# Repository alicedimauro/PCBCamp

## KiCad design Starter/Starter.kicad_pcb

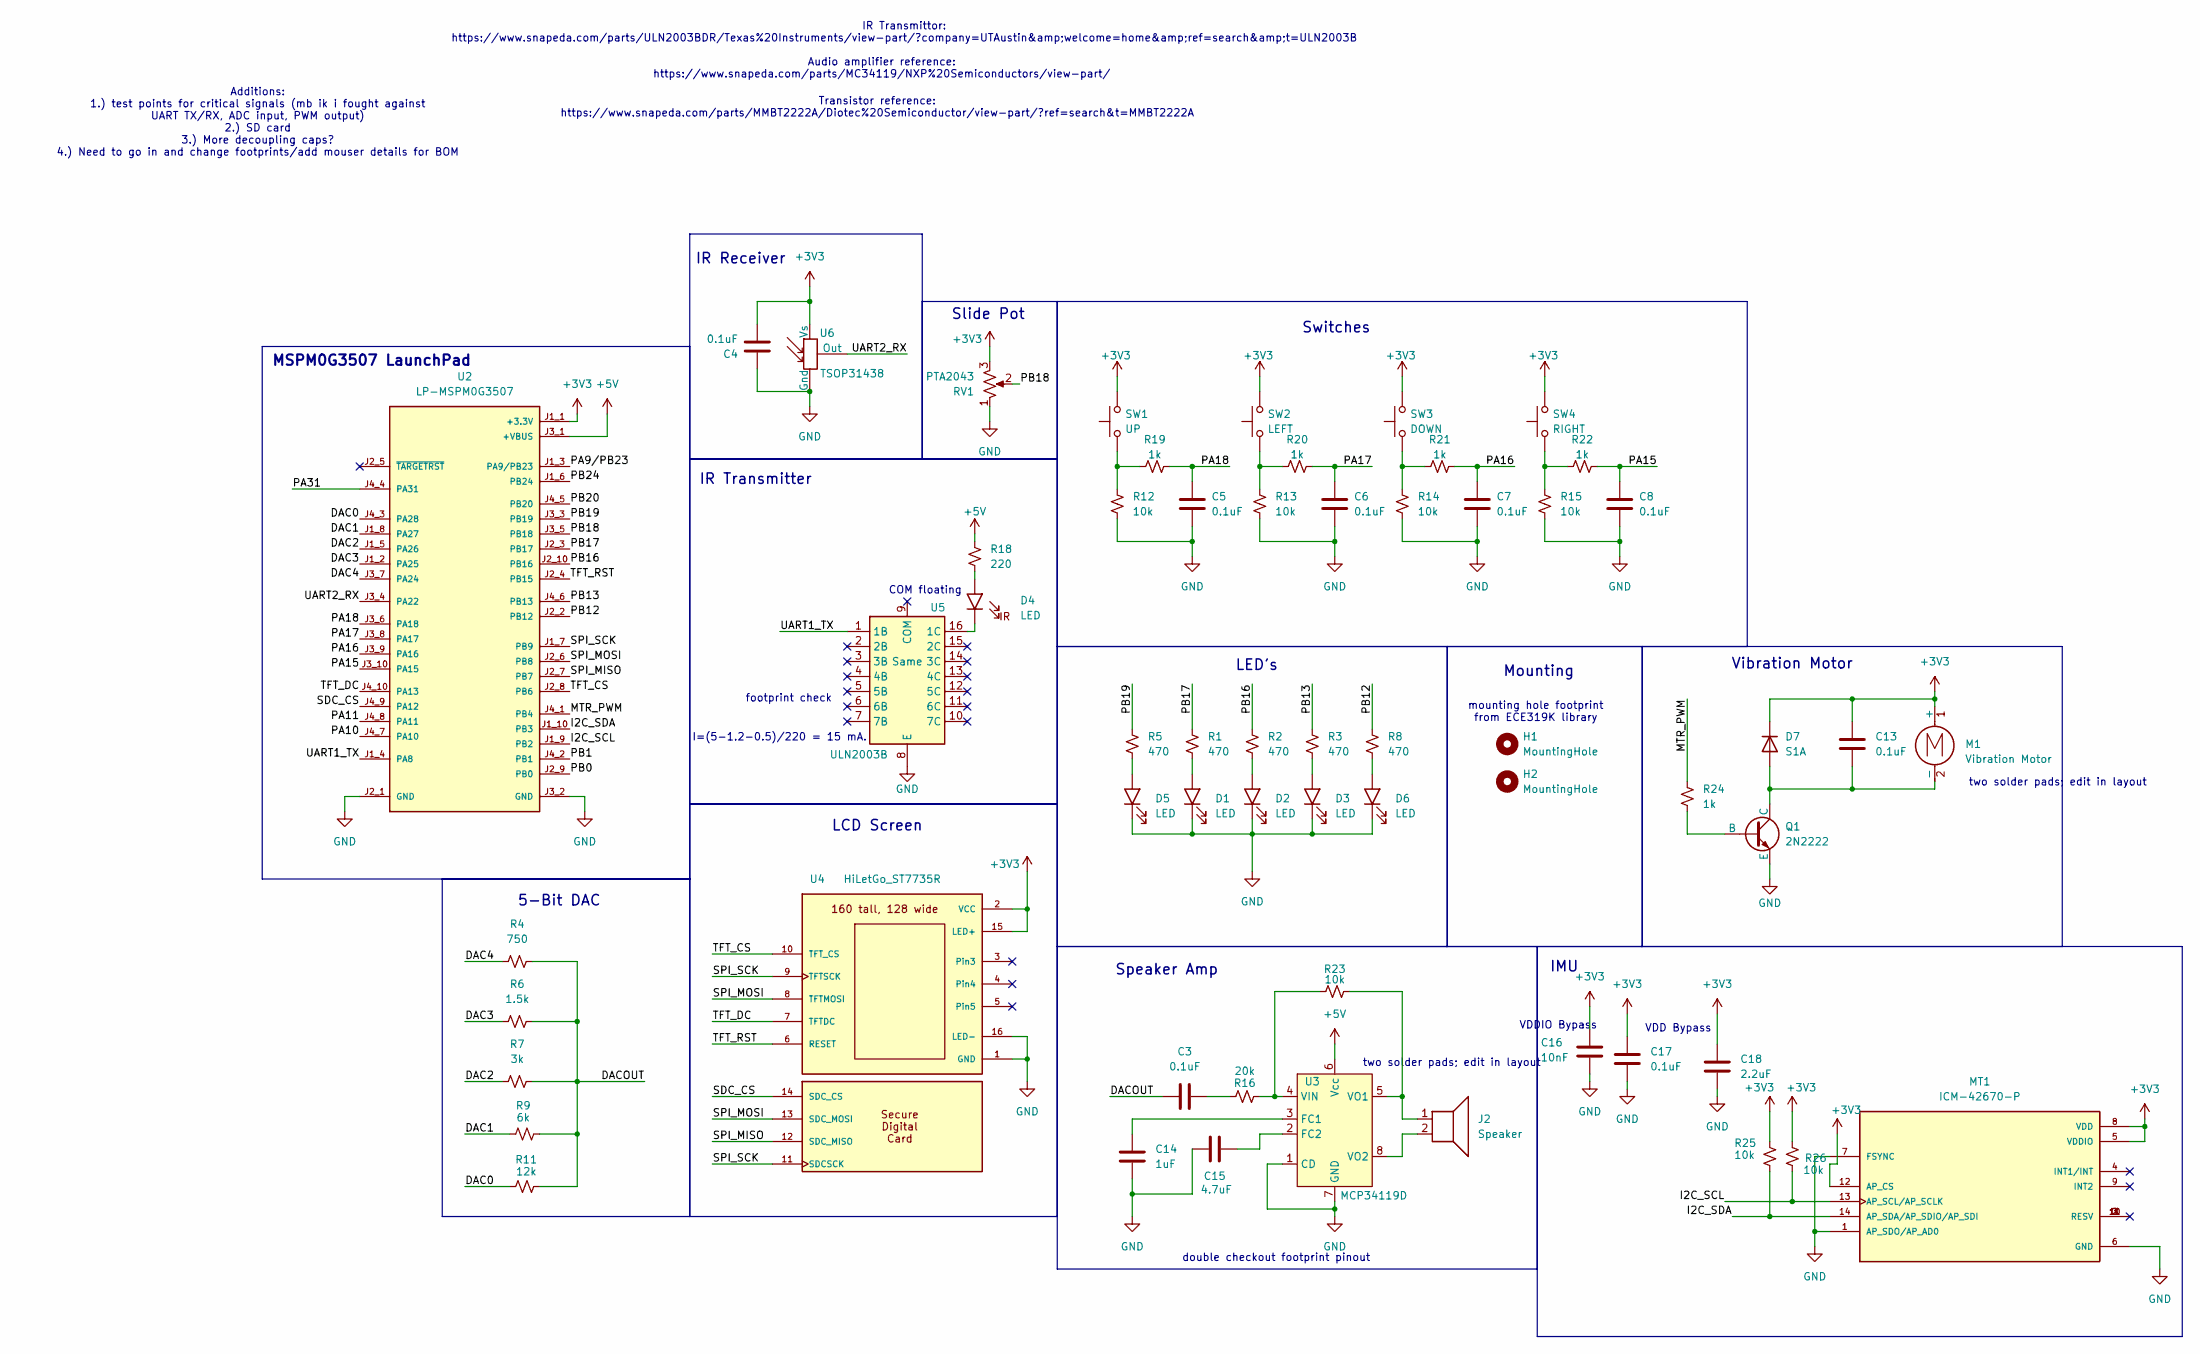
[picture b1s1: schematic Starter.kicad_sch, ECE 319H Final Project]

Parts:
C3, C4, C5, C6, C7, C8, C13, C17: 0.1uF; C_0603_1608Metric_Pad1.08x0.95mm_HandSolder
C14: 1uF; C_0603_1608Metric_Pad1.08x0.95mm_HandSolder
C15: 4.7uF; C_0603_1608Metric_Pad1.08x0.95mm_HandSolder
C16: 10nF; C_0603_1608Metric_Pad1.08x0.95mm_HandSolder
C18: 2.2uF; C_0603_1608Metric_Pad1.08x0.95mm_HandSolder
D1, D2, D3, D5, D6: LED; LED_0805_2012Metric
D4: LED; LED_D5.0mm
D7: S1A; D_SMA; Mouser # 512-S1A
H1, H2: MountingHole; MountingHole_3.2mm_M3
J2: Speaker; Testpoint_1x02_P2.54mm
M1: Vibration Motor; Testpoint_1x02_P2.54mm; Mouser # 316040001
MT1: ICM-42670-P; XDCR_ICM-42670-P; Mouser # 410-ICM-42670-P
Q1: 2N2222; SOT-23; Mouser # MMBT2222A
R1, R2, R3, R5, R8: 470; R_0603_1608Metric_Pad0.98x0.95mm_HandSolder
R4: 750; R_0603_1608Metric_Pad0.98x0.95mm_HandSolder
R6: 1.5k; R_0603_1608Metric_Pad0.98x0.95mm_HandSolder
R7: 3k; R_0603_1608Metric_Pad0.98x0.95mm_HandSolder
R9: 6k; R_0603_1608Metric_Pad0.98x0.95mm_HandSolder
R11: 12k; R_0603_1608Metric_Pad0.98x0.95mm_HandSolder
R12, R13, R14, R15, R23, R25, R26: 10k; R_0603_1608Metric_Pad0.98x0.95mm_HandSolder
R16: 20k; R_0603_1608Metric_Pad0.98x0.95mm_HandSolder
R18: 220; R_0603_1608Metric_Pad0.98x0.95mm_HandSolder
R19, R20, R21, R22, R24: 1k; R_0603_1608Metric_Pad0.98x0.95mm_HandSolder
RV1: PTA2043; PTA2043pot
SW1: UP; SW_SPST_PTS645; Mouser # 506-1977223-1
SW2: LEFT; SW_SPST_PTS645; Mouser # 506-1977223-1
SW3: DOWN; SW_SPST_PTS645; Mouser # 506-1977223-1
SW4: RIGHT; SW_SPST_PTS645; Mouser # 506-1977223-1
U2: LP-MSPM0G3507; ti_LP_MSPM0G3507
U3: MCP34119D; DIP-8_W7.62mm_LongPads
U4: HiLetGo_ST7735R; hiletgo_st7735r
U5: ULN2003B; SOIC127P600X175-16N; Mouser # 511-ULN2003D1013TR
U6: TSOP31438

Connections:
+3V3: C4.2, C13.1, C16.1, C17.1, C18.1, D7.1 (K), M1.1 (+), MT1.5 (VDDIO), MT1.8 (VDD), MT1.12 (AP_CS), R25.1, R26.1, RV1.3, SW1.2, SW2.2, SW3.2, SW4.2, U2.J1_1 (+3.3V), U4.2 (VCC), U4.15 (LED+), U6.2 (Vs)
+5V: R18.1, U2.J3_1 (+VBUS), U3.6 (Vcc)
/DAC0: R11.2, U2.J4_3 (PA28)
/DAC1: R9.2, U2.J1_8 (PA27)
/DAC2: R7.2, U2.J1_5 (PA26)
/DAC3: R6.2, U2.J1_2 (PA25)
/DAC4: R4.2, U2.J3_7 (PA24)
/DACOUT: C3.1, R4.1, R6.1, R7.1, R9.1, R11.1
/I2C_SCL: MT1.13 (AP_SCL/AP_SCLK), R26.2, U2.J1_9 (PB2)
/I2C_SDA: MT1.14 (AP_SDA/AP_SDIO/AP_SDI), R25.2, U2.J1_10 (PB3)
/MTR_PWM: R24.1, U2.J4_1 (PB4)
/PA9/PB23: U2.J1_3 (PA9/PB23)
/PA10: U2.J4_7 (PA10)
/PA11: U2.J4_8 (PA11)
/PA15: C8.1, R22.1, U2.J3_10 (PA15)
/PA16: C7.1, R21.1, U2.J3_9 (PA16)
/PA17: C6.1, R20.1, U2.J3_8 (PA17)
/PA18: C5.1, R19.1, U2.J3_6 (PA18)
/PA31: U2.J4_4 (PA31)
/PB0: U2.J2_9 (PB0)
/PB1: U2.J4_2 (PB1)
/PB12: R8.1, U2.J2_2 (PB12)
/PB13: R3.1, U2.J4_6 (PB13)
/PB16: R2.1, U2.J2_10 (PB16)
/PB17: R1.1, U2.J2_3 (PB17)
/PB18: RV1.2, U2.J3_5 (PB18)
/PB19: R5.1, U2.J3_3 (PB19)
/PB20: U2.J4_5 (PB20)
/PB24: U2.J1_6 (PB24)
/SDC_CS: U2.J4_9 (PA12), U4.14 (SDC_CS)
/SPI_MISO: U2.J2_7 (PB7), U4.12 (SDC_MISO)
/SPI_MOSI: U2.J2_6 (PB8), U4.8 (TFTMOSI), U4.13 (SDC_MOSI)
/SPI_SCK: U2.J1_7 (PB9), U4.9 (TFTSCK), U4.11 (SDCSCK)
/TFT_CS: U2.J2_8 (PB6), U4.10 (TFT_CS)
/TFT_DC: U2.J4_10 (PA13), U4.7 (TFTDC)
/TFT_RST: U2.J2_4 (PB15), U4.6 (RESET)
/UART1_TX: U2.J1_4 (PA8), U5.1 (1B)
/UART2_RX: U2.J3_4 (PA22), U6.3 (Out)
GND: C4.1, C5.2, C6.2, C7.2, C8.2, C14.1, C15.2, C16.2, C17.2, C18.2, D1.1 (K), D2.1 (K), D3.1 (K), D5.1 (K), D6.1 (K), MT1.1 (AP_SDO/AP_AD0), MT1.6 (GND), MT1.7 (FSYNC), Q1.3 (E), R12.2, R13.2, R14.2, R15.2, RV1.1, U2.J2_1 (GND), U2.J3_2 (GND), U3.1 (CD), U3.7 (GND), U4.1 (GND), U4.16 (LED-), U5.8 (E), U6.1 (Gnd)
unnamed: C3.2, R16.2
unnamed: D1.2 (A), R1.2
unnamed: D2.2 (A), R2.2
unnamed: D3.2 (A), R3.2
unnamed: D4.2 (A), R18.2
unnamed: D4.1 (K), U5.16 (1C)
unnamed: D5.2 (A), R5.2
unnamed: D6.2 (A), R8.2
unnamed: C13.2, D7.2 (A), M1.2 (-), Q1.1 (C)
unnamed: Q1.2 (B), R24.2
unnamed: R12.1, R19.2, SW1.1
unnamed: R13.1, R20.2, SW2.1
unnamed: R14.1, R21.2, SW3.1
unnamed: R15.1, R22.2, SW4.1
unnamed: C14.2, U3.3 (FC1)
unnamed: C15.1, U3.2 (FC2)
unnamed: R16.1, R23.2, U3.4 (VIN)
unnamed: J2.1, R23.1, U3.5 (VO1)
unnamed: J2.2, U3.8 (VO2)

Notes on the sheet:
double checkout footprint pinout
VDDIO Bypass
LCD Screen
5-Bit DAC
VDD Bypass
two solder pads; edit in layout
COM floating
IMU
IR Transmitter
I=(5-1.2-0.5)/220 = 15 mA.
LED's
Audio amplifier reference: https://www.snapeda.com/parts/MC34119/NXP%20Semiconductors/view-part/
IR Transmittor: https://www.snapeda.com/parts/ULN2003BDR/Texas%20Instruments/view-part/?company=UTAustin&amp;welcome=home&amp;ref=search&amp;t=ULN2003B
Transistor reference: https://www.snapeda.com/parts/MMBT2222A/Diotec%20Semiconductor/view-part/?ref=search&t=MMBT2222A
MSPM0G3507 LaunchPad
Switches
footprint check
Slide Pot
Vibration Motor
Mounting
mounting hole footprint from ECE319K library
IR Receiver
Additions: 1.) test points for critical signals (mb ik i fought against UART TX/RX, ADC input, PWM output) 2.) SD card 3.) More decoupling caps? 4.) Need to go in and change footprints/add mouser details for BOM
Speaker Amp

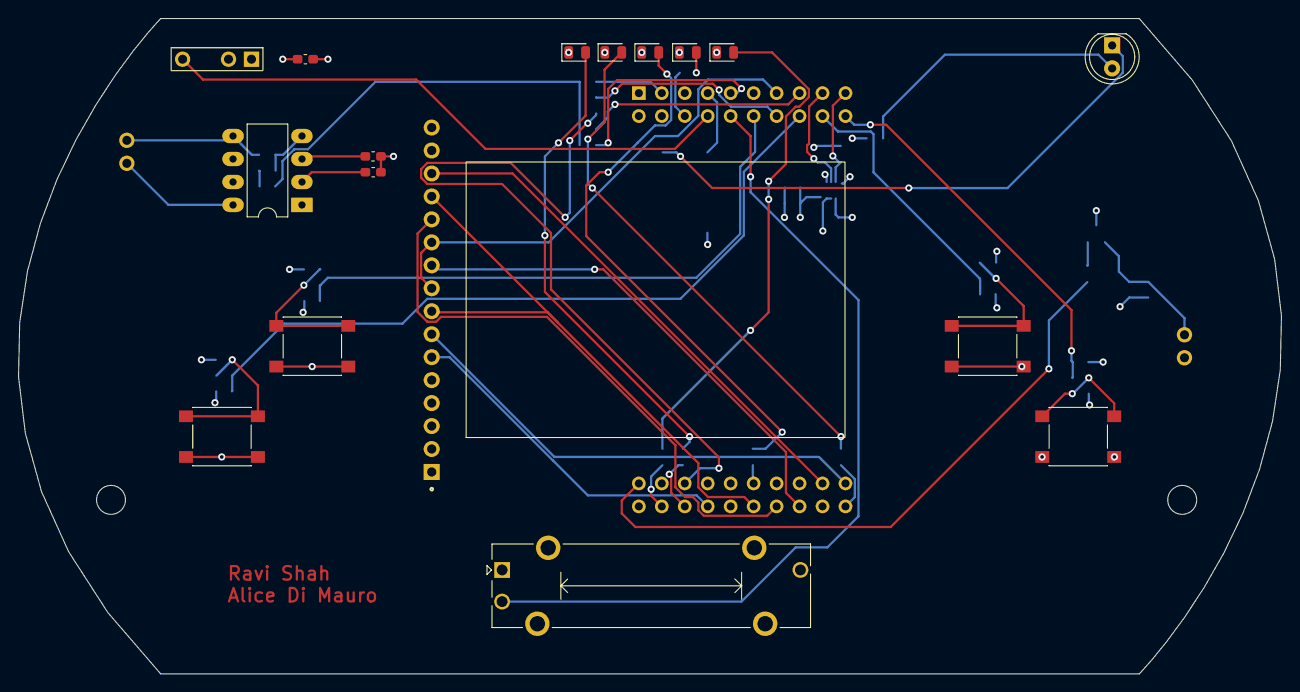
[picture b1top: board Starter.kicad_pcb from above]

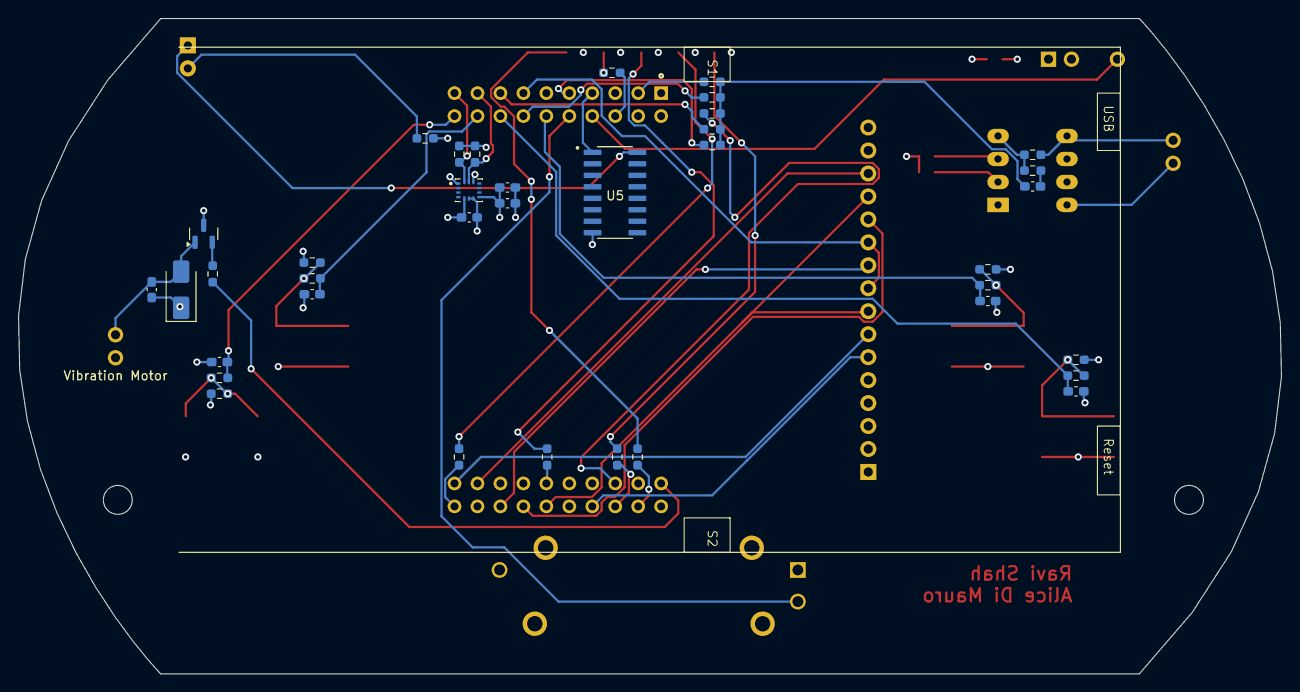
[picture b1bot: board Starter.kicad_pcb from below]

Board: 4 copper layers, 139.7 x 72.5 mm, 59 parts (39 on the bottom side), 50 nets.

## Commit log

2025-04-04 initialize files
2025-04-04 file structure fix
2025-04-04 dumbass
2025-04-04 gitignore
2025-04-04 schematic cleaning
2025-04-04 fix labels and stuff
2025-04-04 more stuff
2025-04-04 add switch debounce
2025-04-04 speaker amp
2025-04-05 wow im dumb
2025-04-05 fix leds
2025-04-05 final sch i think
2025-04-05 schematic cleanup
2025-04-05 structure changes
2025-04-05 corrections listed - I'll fix later
2025-04-05 I like my sch structure more :)
2025-04-05 brain dumped - I'll clean later
2025-04-07 final sch? footprint fixes
2025-04-07 need imu
2025-04-08 footprints added
2025-04-10 Replaced IMU
2025-04-10 THT additions
2025-04-10 update from sch
2025-04-11 initial layout
2025-04-11 Component placements finalized
2025-04-11 fixed silkscreens
2025-04-11 final board! ordered
2025-04-11 all mouser links attached
2025-04-12 added LED p/n
